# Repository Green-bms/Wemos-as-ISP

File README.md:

# Wemos as ISP

 <br>

## Description

Wemos as ISP is an interface card that plugs into Wemos mini board ESP8266, to allow the programming of 8-pin ATtiny 25/45/85 controllers and 14-pin ATtiny 24/44/84 controllers

## Video tutorial
https://youtu.be/ktZU3sbenOU?si=Dj4A4wVRVGfgxN6n <br>

## Hardware
The electronic board project files are found here: <br>
https://github.com/Green-bms/Wemos-as-ISP/tree/master/Wemos%20as%20isp/Kicad <br>
To make or buy the card, the gerber files are here: <br>
https://github.com/Green-bms/Wemos-as-ISP/tree/master/Wemos%20as%20isp/Kicad/export <br>

## Software
The sketch to upload to the Wemos Mini card can be found here: <br>
https://github.com/Green-bms/Wemos-as-ISP/tree/master/Wemos%20as%20isp/Arduino%20ide/Wemos_as_ISP

## Test circuits
To test the correct programming of the ATtiny microcontrollers I created two test circuits for ATtiny85 and ATtiny84.
The wiring diagram is here: <br>
https://github.com/Green-bms/Wemos-as-ISP/blob/master/Attiny%20test/Electrical%20drawing/Attiny%20test%20circuits.pdf
The Arduino IDE sketches to load into the Attiny microcontrollers are here: <br>
https://github.com/Green-bms/Wemos-as-ISP/tree/master/Attiny%20test/Arduino%20IDE <br>

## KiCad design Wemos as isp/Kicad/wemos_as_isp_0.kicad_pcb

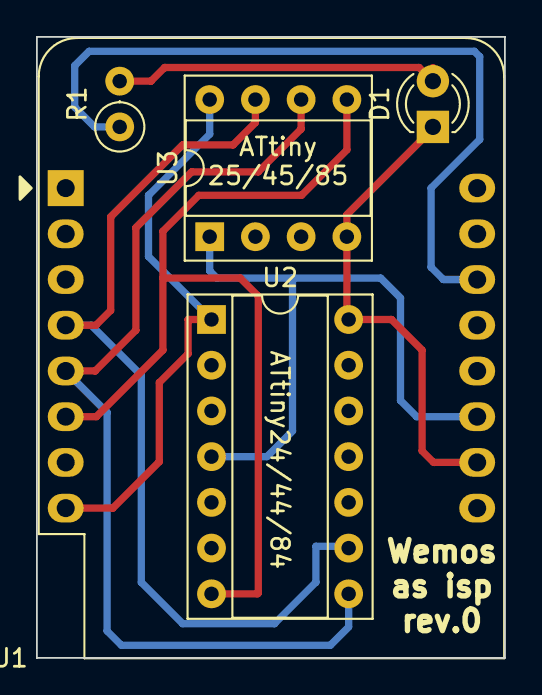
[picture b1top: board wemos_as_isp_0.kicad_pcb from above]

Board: 2 copper layers, 26.0 x 34.5 mm, 5 parts (0 on the bottom side), 8 nets.

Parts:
D1: LED; LED_D3.0mm
R1: 330; R_Axial_DIN0207_L6.3mm_D2.5mm_P2.54mm_Vertical
U1: WeMos_D1_mini; WEMOS_D1_mini_light
U2: ATTINY84A-PU; DIP-14_W7.62mm_Socket
U3: ATTINY85-20PU; DIP-8_W7.62mm_Socket

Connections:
/miso: U1.5, U2.8, U3.6
/mosi: U1.6, U2.7, U3.5
/reset: U1.11, U2.4, U3.1
/sck: U1.4, U2.9, U3.7
unnamed: D1.1, U1.10, U2.14, U3.4
unnamed: D1.2, R1.2
unnamed: R1.1, U1.14
unnamed: U1.8, U2.1, U3.8

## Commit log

2024-03-06 Update README.md
    added video
